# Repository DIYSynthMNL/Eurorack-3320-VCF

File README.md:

# Eurorack-3320-VCF

A Eurorack 4-pole low-pass voltage-controlled filter based on the [AS3320](https://electricdruid.net/product/as3320-vcf/) chip from Electric Druid — a high-performance 4-pole VCF (CEM3372 family). 12-octave cutoff sweep range and voltage-controlled resonance from zero to oscillation.

## Features

- **4-pole (24 dB/oct) low-pass response** using all four AS3320 filter stages
- **12-octave cutoff range** with smooth exponential control
- **Voltage-controlled resonance** — from zero to self-oscillation
- **Cutoff frequency** controlled by a panel pot + CV input with attenuation
- **Resonance** controlled by a panel pot + CV input with attenuation
- **Three calibration trims**:
  - Freq CV gain trim (RV2)
  - Reso CV gain trim (RV5)
  - Output amplitude trim (RV1)
- Eurorack ±12V power via either 16-pin IDC or 3-pin JST connector
- "Sequential Pro One"-style output buffer with AC coupling
- Audio inputs handle 10 Vpp directly (no input AC coupling needed)

## Inputs and outputs

| Jack | Range | Notes |
|---|---|---|
| Sig In | 10 Vpp | Through 100K input buffer, then to filter chain via 91K |
| Freq CV | 10 Vpp | Mixed with front-panel Freq Control via summing amp |
| Res CV | 10 Vpp | Mixed with front-panel Reso Control via summing amp |
| Sig Out | ≤9 Vpp | AC-coupled, gain-2 output buffer with amplitude trim |

## Block diagram

```
Sig In ─► [TL072 input buffer, U1A] ─► [91K] ─► AS3320 IN1
                                                  │
                                                  ▼ Stage 1 (LP)
                                                IN2 ─► Stage 2 (LP) ─► IN3 ─► Stage 3 (LP) ─► IN4 ─► Stage 4 (LP) ─► Out4
                                                                                                                       │
                                                                                                                       ▼
                                                                                                              [2.2 µF AC couple]
                                                                                                                       │
                                                                                                                       ▼
                                                                                                       [TL072 gain-2 + amp trim] ─► Sig Out
                                                                                                                       │
                                                                                                                       └─► [3.3K] ─► AS3320 Vres (resonance feedback)

Freq Control pot ─► [100K] ─┬─► [TL074 summing amp + RV2 gain trim] ─► AS3320 VCFI (pin 12)
Freq CV jack (RV4 atten) ──►┘

Reso Control pot ─► [100K] ─┬─► [TL074 stage 1 + RV5 gain trim] ─► [TL074 stage 2, 100K/150K] ─► [3.3K] ─► AS3320 Ires (pin 9)
Reso CV jack (RV7 atten) ──►┘

Power: Eurorack ±12V ─► local +12V (filtered) and −12V (filtered)
       AS3320 VEE: −12V via REE (R22 = 1.2K) → internal −2.7V regulator
       AS3320 VCC: +12V direct
       Filter stage Rb resistors (R12/R13/R14): 220K to −12V (note: 240K recommended for +12V VCC per datasheet)
       Filter timing caps (C3–C6): 270 pF each (cap1–cap4 pins)
```

## Power

- Eurorack ±12V via **J5** (3-pin JST) or **J6** (16-pin IDC) — populate one
- D1 / D2: reverse-polarity protection
- C9 / C12 (22 µF): bulk rail decoupling
- C10 / C11 (100 nF): op-amp supply decoupling
- **R22 = 1.2 kΩ — AS3320 VEE current limit resistor.** *Required* — the chip has an internal −2.7V regulator and must not see more than ~8 mA on the VEE pin.

REE formula from datasheet: **REE = (|VEE| − 2.7) / 0.008**

| VEE supply | REE |
|---|---|
| −10V | 910 Ω |
| −12V | 1.2 kΩ ← *used here* |
| −15V | 1.5 kΩ |

## Calibration

Three trim pots. Adjust in order, with the module warmed up ~5 minutes.

**RV1 — Output amplitude trim.** Sets final output level. The chip's max output is roughly VCC − 3V (so ~9 Vpp at +12V). Trim until output reaches 10 Vpp at modest input + maximum resonance.

**RV2 — Freq CV gain trim.** Sets the gain of the Freq CV path. Tune to taste — full range of the Freq CV jack should produce a musically-useful filter sweep.

**RV5 — Reso CV gain trim.** Sets the gain of the Reso CV path. At maximum reso CV, filter should reach self-oscillation; at minimum, no resonance.

Procedure:
1. With the module warmed up, set Freq Control to mid, Reso Control to min, no inputs patched.
2. Patch a steady audio signal (sawtooth from a VCO, ~−10 dB) into Sig In and a scope on Sig Out.
3. Adjust RV1 until peak output is ~10 Vpp without clipping.
4. Sweep Freq Control by hand; should hear the filter open and close smoothly.
5. Raise Reso Control — should hear the resonant peak grow, eventually self-oscillating at high values.
6. With a 0–5V LFO patched into Reso CV (jack pot RV7 fully open), adjust RV5 to get the same self-oscillation behavior when CV-driven as you got from the panel pot.
7. With a 0–5V LFO patched into Freq CV (jack pot RV4 fully open), adjust RV2 to get a similar full-range sweep when CV-driven.

## Design references

Local archived copies live in [`references/`](references/) so this repo stays useful if the upstream links die.

- **AS3320 datasheet** — [local copy](references/AS3320-alfatriode-2023.pdf) · [upstream (alfatriode.lv)](https://alfatriode.lv/eng/sc/AS3320.pdf) — definitive reference for the chip
- [Electric Druid AS3320 product page](https://electricdruid.net/product/as3320-vcf/)
- [Electric Druid multimode filter notes](https://electricdruid.net/multimode-filters-part-1-reconfigurable-filters/) — the AS3320 can be wired for LPF / HPF / BPF / APF; this design is LPF only
- Output buffer topology adapted from the Sequential Pro One synth
- [Falstad simulations](falstad/) of input, frequency control, resonance control, and output sub-circuits

## Build status

What's ready for builders today, and what's still on the TODO list:

**Production assets**

- [x] Schematic — Rev 0.1.5 ([PDF](Schematic%20PDFs/3320-VCF_Schematic-Rev-0.1.5.pdf))
- [ ] PCB layout — rev 0.1.0 separated for fab in `kicad/Separate boards/rev0.1.0/`; schematic has advanced to 0.1.5, **re-separation pending**
- [ ] Gerber files for fabrication — none yet
- [ ] BOM — none yet
- [ ] Final front panel (SVG/PDF for fab) — none yet
- [ ] License — none yet

**Prototype assets**

- [x] 3D-printed prototype panel STL — [3320_VCF.stl](3D%20Printed%20Panel/3320_VCF.stl)
- [x] Falstad simulations — [falstad/](falstad/)

**Documentation**

- [x] Photos of the assembled module — see [photos/](photos/)
- [ ] Demo video — none yet
- [ ] Build / assembly instructions — none yet
- [x] Calibration / tuning notes — see "Calibration" section above

Want to help fill a gap (build photos, gerbers, an assembly guide)? Open an issue or PR.

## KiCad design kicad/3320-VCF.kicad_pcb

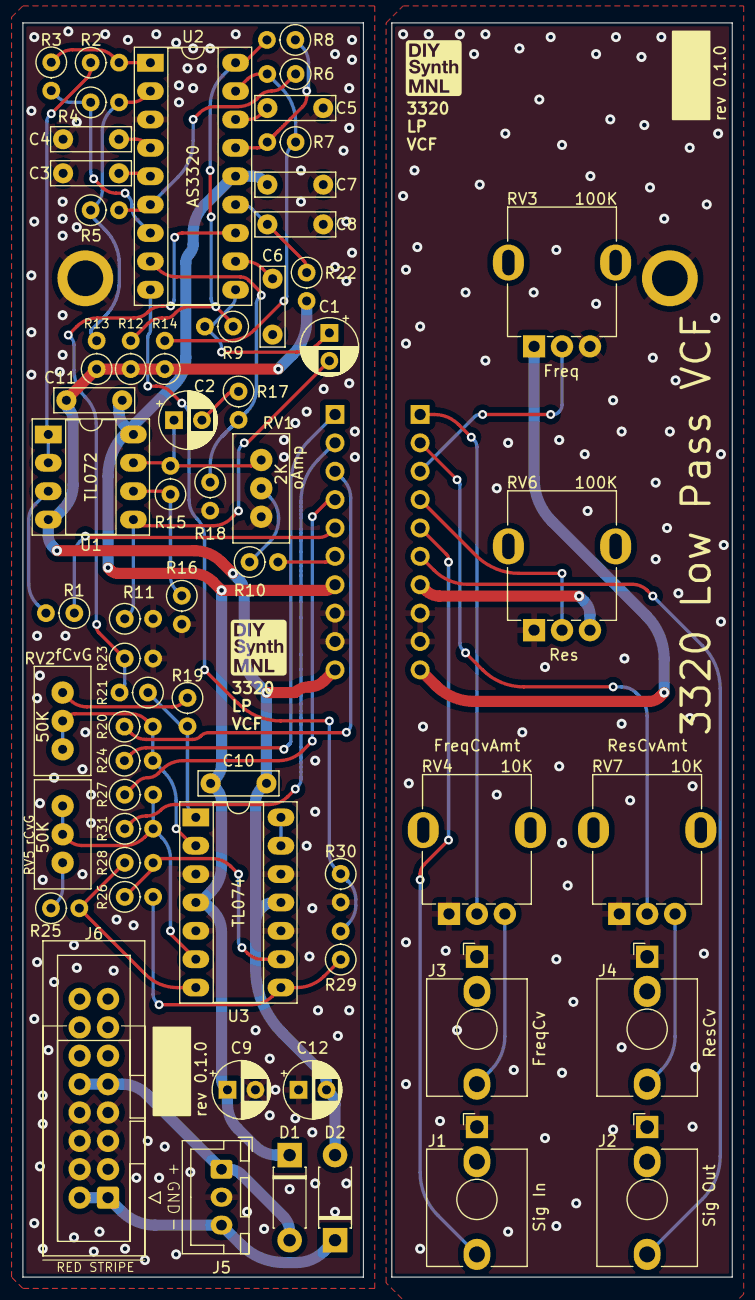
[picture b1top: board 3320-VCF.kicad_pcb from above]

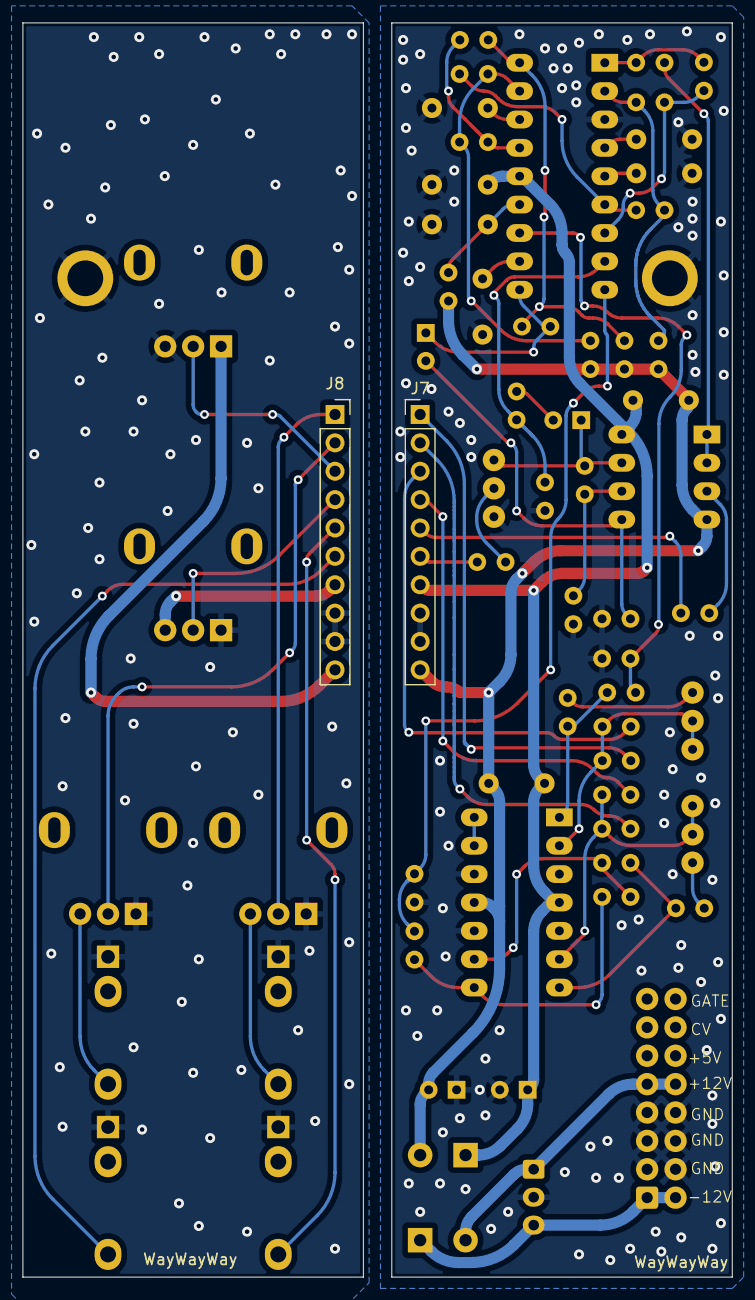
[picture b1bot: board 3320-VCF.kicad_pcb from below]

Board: 2 copper layers, 63.5 x 112.3 mm, 67 parts (2 on the bottom side), 54 nets.

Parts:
A: Board
B: Board
C1, C2: 2.2uF; CP_Radial_D5.0mm_P2.50mm
C3, C4, C5, C6: 270pF; C_Rect_L7.0mm_W2.0mm_P5.00mm_BigPads
C7, C8, C10, C11: 100nF; C_Rect_L7.0mm_W2.0mm_P5.00mm_BigPads
C9, C12: 22uF; CP_Radial_D5.0mm_P2.50mm
D1, D2: D_DO-41_SOD81_P7.62mm_Horizontal_BigPads
H1, H2: MountingHole_Pad; MountingHole_M3_Standoff_Pad
J1: Sig In; AudioJack_3.5mm_long_pads
J2: Sig Out; AudioJack_3.5mm_long_pads
J3: FreqCv; AudioJack_3.5mm_long_pads
J4: ResCv; AudioJack_3.5mm_long_pads
J5: EuroPower_JST_3P; Eurorack_power_jst_3P
J6: EURO_PWR_16P; IDC-Header_2x08_P2.54mm_Vertical
J7: Main; PinHeader_1x10_P2.54mm_Vertical
J8: Ctrl; PinSocket_1x10_P2.54mm_Vertical
R1, R3, R5, R7, R9, R16, R20, R21, R24, R26, R27, R28, R31: 100K; R_Axial_DIN0207_L6.3mm_D2.5mm_P2.54mm_Vertical
R2, R4, R6, R8: 91K; R_Axial_DIN0207_L6.3mm_D2.5mm_P2.54mm_Vertical
R10: 1K; R_Axial_DIN0207_L6.3mm_D2.5mm_P2.54mm_Vertical
R11, R19, R25: 68K; R_Axial_DIN0207_L6.3mm_D2.5mm_P2.54mm_Vertical
R12, R13, R14: 220K; R_Axial_DIN0207_L6.3mm_D2.5mm_P2.54mm_Vertical
R15: 330K; R_Axial_DIN0207_L6.3mm_D2.5mm_P2.54mm_Vertical
R17: 51K; R_Axial_DIN0207_L6.3mm_D2.5mm_P2.54mm_Vertical
R18: 3K3; R_Axial_DIN0207_L6.3mm_D2.5mm_P2.54mm_Vertical
R22: 1K2; R_Axial_DIN0207_L6.3mm_D2.5mm_P2.54mm_Vertical
R23: 1K8; R_Axial_DIN0207_L6.3mm_D2.5mm_P2.54mm_Vertical
R29: 150K; R_Axial_DIN0207_L6.3mm_D2.5mm_P2.54mm_Vertical
R30: 3.3K; R_Axial_DIN0207_L6.3mm_D2.5mm_P2.54mm_Vertical
RV1: 2K; Potentiometer_Bourns_3296W_Vertical_BigPads
RV2, RV5: 50K; Potentiometer_Bourns_3296W_Vertical_BigPads
RV3, RV6: 100K; Potentiometer_RV09_BigPads
RV4, RV7: 10K; Potentiometer_RV09_BigPads
U1: TL072; DIP-8_W7.62mm_Socket_LongPads
U2: AS3320; DIP-18_W7.62mm_Socket_LongPads
U3: TL074; DIP-14_W7.62mm_Socket_LongPads

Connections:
+12V: C7.1, C9.1, C10.1, C11.1, D1.1 (K), J7.7, U1.8 (V+), U2.14 (VCC), U3.4 (V+)
-12V: C10.2, C11.2, C12.2, D2.2 (A), J7.10, R12.1, R13.1, R14.1, R22.2, U1.4 (V-), U3.11 (V-)
/3320_Control_Board/CB_+12V: J8.7, RV6.3
/3320_Control_Board/CB_-12V: J8.10, RV3.1
/3320_Control_Board/CB_GND: H2.1, J1.S, J2.S, J3.S, J4.S, J8.8, J8.9, RV3.3, RV4.1, RV6.1, RV7.1
/3320_Control_Board/Freq_control: J8.3, RV3.2
/3320_Control_Board/Freq_cv: J8.1, RV4.2
/3320_Control_Board/Res_control: J8.4, RV6.2
/3320_Control_Board/Res_cv: J8.2, RV7.2
/3320_Control_Board/Sig_in: J1.T, J8.5
/3320_Control_Board/Sig_out: J2.T, J8.6
/3320_Main_Board/3320_Cap1: C3.1, U2.5 (Cap1)
/3320_Main_Board/3320_Cap2: C4.1, U2.4 (Cap2)
/3320_Main_Board/3320_Cap3: C5.1, U2.16 (Cap3)
/3320_Main_Board/3320_Cap4: C6.1, U2.11 (Cap4)
/3320_Main_Board/3320_Freq_control_in: R21.2, R23.1, U2.12 (Freq_control_in)
/3320_Main_Board/3320_IN1: R2.2, R3.1, U2.1 (IN1)
/3320_Main_Board/3320_IN2: R4.2, R5.1, R13.2, U2.2 (IN2)
/3320_Main_Board/3320_IN3: R6.2, R7.1, R14.2, U2.17 (IN3)
/3320_Main_Board/3320_IN4: R8.2, R9.1, R12.2, U2.18 (IN4)
/3320_Main_Board/3320_Out1: R3.2, R4.1, U2.7 (Out1)
/3320_Main_Board/3320_Out2: R5.2, R6.1, U2.6 (Out2)
/3320_Main_Board/3320_Out3: R7.2, R8.1, U2.15 (Out3)
/3320_Main_Board/3320_Out4: C1.1, R9.2, U2.10 (Out4)
/3320_Main_Board/3320_Reso_control_in: R29.2, R30.1, U2.9 (Reso_control_in)
/3320_Main_Board/3320_Vres: R17.2, R18.1, U2.8 (Vres)
/3320_Main_Board/+12V_IN: D1.2 (A), J5.1 (+12v), J6.9 (+12V), J6.10 (+12V)
/3320_Main_Board/-12V_IN: D2.1 (K), J5.3 (-12v), J6.1 (-12V), J6.2 (-12V)
/3320_Main_Board/Freq_control: J7.3, R20.1
/3320_Main_Board/Freq_cv: J7.1, R24.1
/3320_Main_Board/Res_control: J7.4, R27.1
/3320_Main_Board/Res_cv: J7.2, R31.1
/3320_Main_Board/Sig_in: J7.5, R1.1
/3320_Main_Board/Sig_out: J7.6, R10.2
GND: C3.2, C4.2, C5.2, C6.2, C7.2, C8.2, C9.2, C12.1, H1.1, J5.2 (GND), J6.3 (GND), J6.4 (GND), J6.5 (GND), J6.6 (GND), J6.7 (GND), J6.8 (GND), J7.8, J7.9, R11.2, R16.2, R18.2, R23.2, R30.2, RV1.1, U2.3 (GND), U3.3 (+), U3.5 (+), U3.10 (+), U3.12 (+)
unnamed: C2.1, R15.2, RV1.3, U1.7
unnamed: C2.2, R17.1
unnamed: J3.T, RV4.3
unnamed: J4.T, RV7.3
unnamed: R10.1, RV1.2
unnamed: R19.1, RV2.3
unnamed: R19.2, R21.1, U3.1
unnamed: R25.1, RV5.3
unnamed: R25.2, R28.1, U3.7
unnamed: R26.2, R29.1, U3.8
unnamed: R1.2, U1.3 (+)
unnamed: R2.1, U1.1, U1.2 (-)
unnamed: C1.2, R11.1, U1.5 (+)
unnamed: R15.1, R16.1, U1.6 (-)
unnamed: C8.1, R22.1, U2.13 (VEE)
unnamed: R20.2, R24.2, RV2.1, RV2.2, U3.2 (-)
unnamed: R27.2, R31.2, RV5.1, RV5.2, U3.6 (-)
unnamed: R26.1, R28.2, U3.9 (-)
unnamed: U3.13 (-), U3.14

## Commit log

2024-01-22 drawn schematic rev 0.1.0
2024-01-22 schematic updated
2024-01-23 Added Schematic Revision 0.1.1
2024-01-23 added Schematic rev 0.1.1 pdf
2024-01-24 added schematic revision 0.1.2
2024-02-15 added schem rev 0.1.3
2024-02-16 assigned footprints
2024-02-16 added pcb rev 0.1.0
2024-02-16 updated pcb revision 0.1.0
2024-02-16 updated pcb rev 0.1.0
2024-02-16 added pcb rev 0.1.0 separate boards
2024-02-16 generated pcbway gerber zips
2024-02-16 added 3d printed front panel
2024-04-09 3d printed panel updated
2025-03-11 Add schematic revision 0.1.5
2026-05-14 Clean up repo cruft
2026-05-14 Add Build status checklist to README
2026-05-14 Fix Build status link path case
2026-05-14 Rewrite Build status with per-module accuracy
2026-05-14 Add photos/ placeholder for assembled-module shots
2026-05-14 Add assembled-module photos and update README hero
2026-05-14 Add JPGs converted from raws and clean photo dirs
2026-05-14 Rename photos to descriptive names; pick hero images
2026-05-14 Expand README with features, I/O table, block diagram, calibration, datasheet references
2026-05-14 Add references/ folder with archived AS3320 datasheet
    Upstream alfatriode.lv links can rot. README now points at the local
    copy and the upstream URL side by side.
2026-05-15 fix: correct REE formula divisor in schematic comment
